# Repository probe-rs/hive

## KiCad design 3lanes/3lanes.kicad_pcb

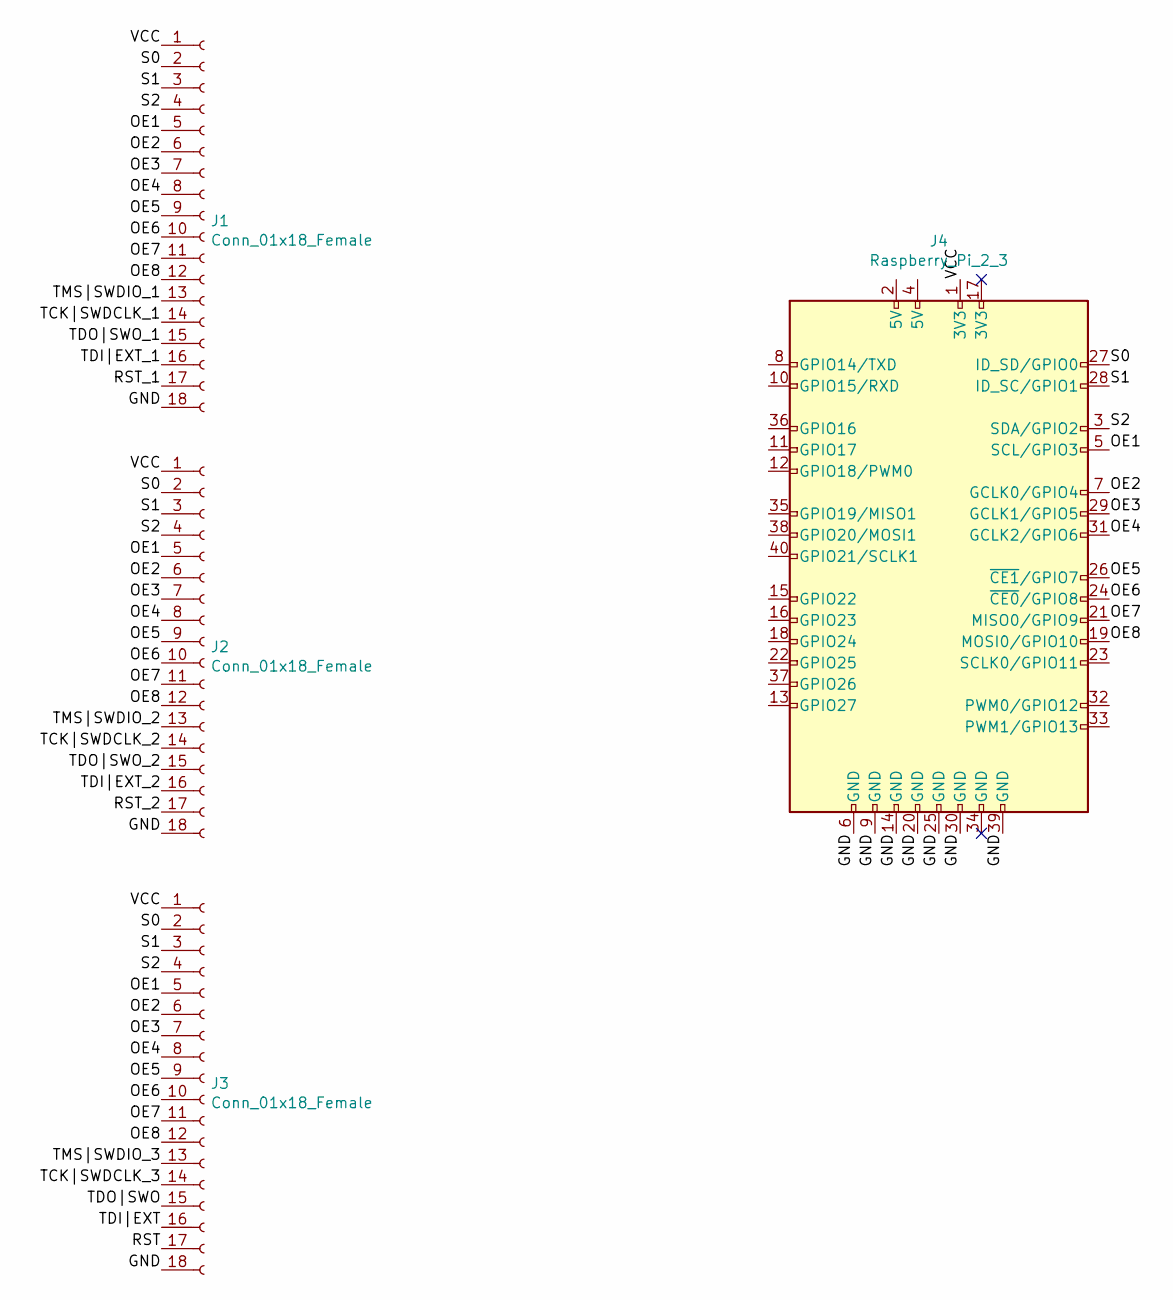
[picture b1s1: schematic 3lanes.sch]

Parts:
J1, J2, J3: Conn_01x18_Female
J4: Raspberry_Pi_2_3

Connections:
/GND: J1.18, J2.18, J3.18, J4.6 (GND), J4.9 (GND), J4.14 (GND), J4.20 (GND), J4.25 (GND), J4.30 (GND), J4.39 (GND)
/OE1: J1.5, J2.5, J3.5, J4.5 (SCL/GPIO3)
/OE2: J1.6, J2.6, J3.6, J4.7 (GCLK0/GPIO4)
/OE3: J1.7, J2.7, J3.7, J4.29 (GCLK1/GPIO5)
/OE4: J1.8, J2.8, J3.8, J4.31 (GCLK2/GPIO6)
/OE5: J1.9, J2.9, J3.9, J4.26 (~CE1~/GPIO7)
/OE6: J1.10, J2.10, J3.10, J4.24 (~CE0~/GPIO8)
/OE7: J1.11, J2.11, J3.11, J4.21 (MISO0/GPIO9)
/OE8: J1.12, J2.12, J3.12, J4.19 (MOSI0/GPIO10)
/RST: J3.17
/RST_1: J1.17
/RST_2: J2.17
/S0: J1.2, J2.2, J3.2, J4.27 (ID_SD/GPIO0)
/S1: J1.3, J2.3, J3.3, J4.28 (ID_SC/GPIO1)
/S2: J1.4, J2.4, J3.4, J4.3 (SDA/GPIO2)
/TCK|SWDCLK_1: J1.14
/TCK|SWDCLK_2: J2.14
/TCK|SWDCLK_3: J3.14
/TDI|EXT: J3.16
/TDI|EXT_1: J1.16
/TDI|EXT_2: J2.16
/TDO|SWO: J3.15
/TDO|SWO_1: J1.15
/TDO|SWO_2: J2.15
/TMS|SWDIO_1: J1.13
/TMS|SWDIO_2: J2.13
/TMS|SWDIO_3: J3.13
/VCC: J1.1, J2.1, J3.1, J4.1 (3V3)

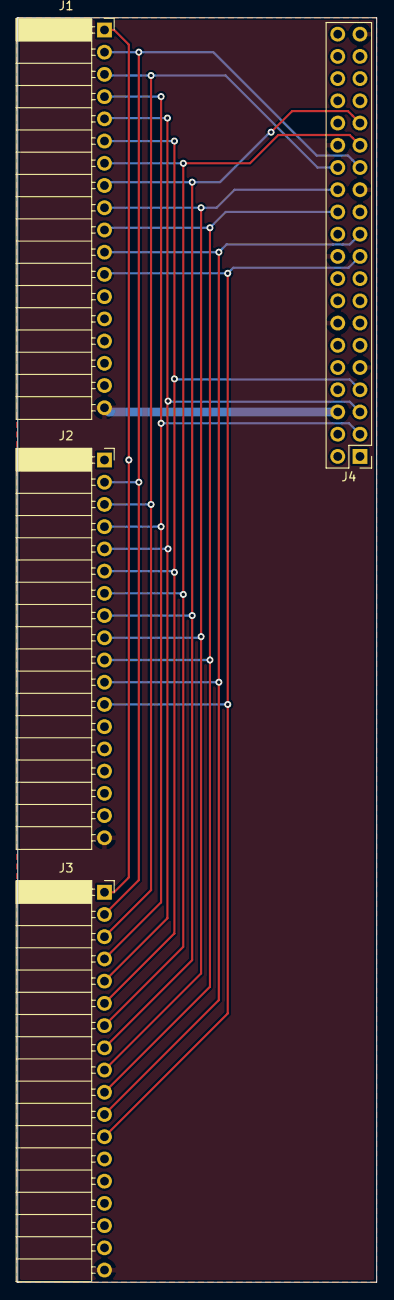
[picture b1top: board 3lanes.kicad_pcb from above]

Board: 2 copper layers, 41.0 x 144.5 mm, 4 parts (0 on the bottom side), 13 nets.

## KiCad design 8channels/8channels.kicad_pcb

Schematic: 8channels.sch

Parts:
C1, C2, C3, C4, C5: 0.1u; C_0402_1005Metric
C101, C102: 1u; C_0402_1005Metric
J1: Conn_01x18_Female; PinSocket_2x10_P2.54mm_Horizontal
J2: Conn_01x18_Male; PinHeader_2x10_P2.54mm_Horizontal
P1, P2: PCIEX1_02X18; 10018784-10200TLF
R101: 10k; R_0402_1005Metric
U1, U2, U3, U4, U5: SN74CB3Q3251PWR; R-PVQFN-N16
U101: MIC5353-3.3YMT; MLF-6-1EP_1.6x1.6mm_P0.5mm_EP0.5x1.26mm

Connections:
+5V: C101.1, J1.1, J2.1, U101.3
/OE: J2.5, R101.2, U1.7 (~OE), U2.7 (~OE), U3.7 (~OE), U4.7 (~OE), U5.7 (~OE), U101.1
/OE2: J1.5, J2.6
/OE3: J1.6, J2.7
/OE4: J1.7, J2.8
/OE5: J1.8, J2.9
/OE6: J1.9, J2.10
/OE7: J1.10, J2.11
/OE8: J1.11, J2.12
/RST: J1.19, J2.19, U5.5 (A)
/RST_1: P2.B15 (P30), U5.4 (B1)
/RST_2: P2.B11 (P22), U5.3 (B2)
/RST_3: P2.B7 (P14), U5.2 (B3)
/RST_4: P2.B3 (P6), U5.1 (B4)
/RST_5: P1.B15 (P30), U5.15 (B5)
/RST_6: P1.B11 (P22), U5.14 (B6)
/RST_7: P1.B7 (P14), U5.13 (B7)
/RST_8: P1.B3 (P6), U5.12 (B8)
/S0: J1.2, J2.2, U1.11 (S0), U2.11 (S0), U3.11 (S0), U4.11 (S0), U5.11 (S0)
/S1: J1.3, J2.3, U1.10 (S1), U2.10 (S1), U3.10 (S1), U4.10 (S1), U5.10 (S1)
/S2: J1.4, J2.4, U1.9 (S2), U2.9 (S2), U3.9 (S2), U4.9 (S2), U5.9 (S2)
/TCK|SWDCLK: J1.16, J2.16, U2.5 (A)
/TCK|SWDCLK_1: P2.A14 (P27), U2.4 (B1)
/TCK|SWDCLK_2: P2.A10 (P19), U2.3 (B2)
/TCK|SWDCLK_3: P2.A6 (P11), U2.2 (B3)
/TCK|SWDCLK_4: P2.A2 (P3), U2.1 (B4)
/TCK|SWDCLK_5: P1.A14 (P27), U2.15 (B5)
/TCK|SWDCLK_6: P1.A10 (P19), U2.14 (B6)
/TCK|SWDCLK_7: P1.A6 (P11), U2.13 (B7)
/TCK|SWDCLK_8: P1.A2 (P3), U2.12 (B8)
/TDI|EXT: J1.18, J2.18, U4.5 (A)
/TDI|EXT_1: P2.B14 (P28), U4.4 (B1)
/TDI|EXT_2: P2.B10 (P20), U4.3 (B2)
/TDI|EXT_3: P2.B6 (P12), U4.2 (B3)
/TDI|EXT_4: P2.B2 (P4), U4.1 (B4)
/TDI|EXT_5: P1.B14 (P28), U4.15 (B5)
/TDI|EXT_6: P1.B10 (P20), U4.14 (B6)
/TDI|EXT_7: P1.B6 (P12), U4.13 (B7)
/TDI|EXT_8: P1.B2 (P4), U4.12 (B8)
/TDO|SWO: J1.17, J2.17, U3.5 (A)
/TDO|SWO_1: P2.B13 (P26), U3.4 (B1)
/TDO|SWO_2: P2.B9 (P18), U3.3 (B2)
/TDO|SWO_3: P2.B5 (P10), U3.2 (B3)
/TDO|SWO_4: P2.B1 (P2), U3.1 (B4)
/TDO|SWO_5: P1.B13 (P26), U3.15 (B5)
/TDO|SWO_6: P1.B9 (P18), U3.14 (B6)
/TDO|SWO_7: P1.B5 (P10), U3.13 (B7)
/TDO|SWO_8: P1.B1 (P2), U3.12 (B8)
/TMS|SWDIO: J1.15, J2.15, U1.5 (A)
/TMS|SWDIO_1: P2.A13 (P25), U1.4 (B1)
/TMS|SWDIO_2: P2.A9 (P17), U1.3 (B2)
/TMS|SWDIO_3: P2.A5 (P9), U1.2 (B3)
/TMS|SWDIO_4: P2.A1 (P1), U1.1 (B4)
/TMS|SWDIO_5: P1.A13 (P25), U1.15 (B5)
/TMS|SWDIO_6: P1.A9 (P17), U1.14 (B6)
/TMS|SWDIO_7: P1.A5 (P9), U1.13 (B7)
/TMS|SWDIO_8: P1.A1 (P1), U1.12 (B8)

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
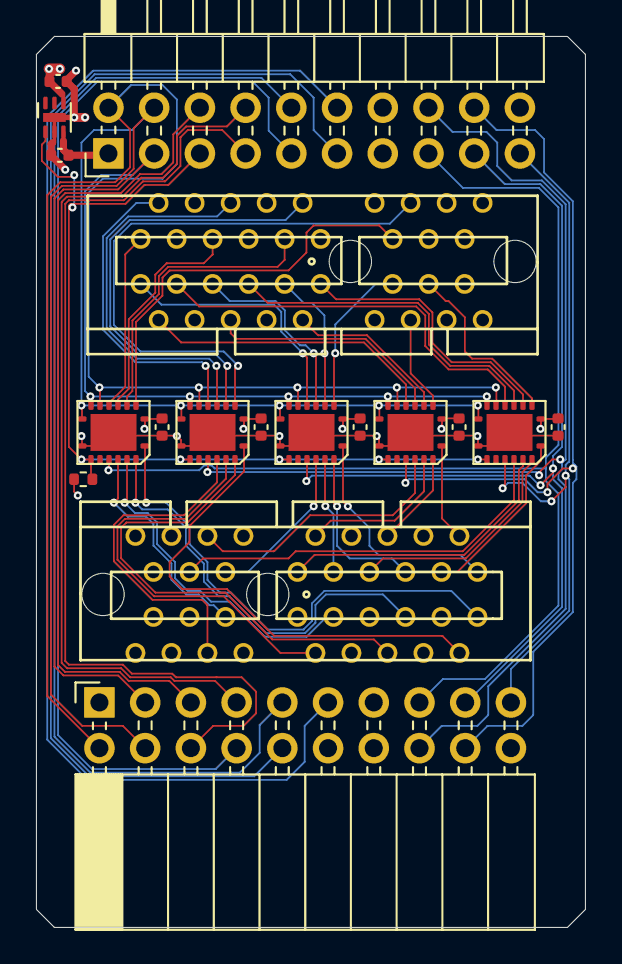
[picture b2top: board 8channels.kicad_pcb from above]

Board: 4 copper layers, 30.5 x 49.5 mm, 18 parts (0 on the bottom side), 59 nets.

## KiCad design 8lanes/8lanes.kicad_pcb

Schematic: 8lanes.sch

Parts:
C101, C102: 47u; C_1206_3216Metric
C103, C104, C105, C106, C107, C108, C109, C110, C111, C112, C113, C114, C115, C116: 0.1u; C_0402_1005Metric
J101, J102, J105, J106, J109, J110, J113, J114: Conn_01x20_Female; PinSocket_2x10_P2.54mm_Horizontal
J103, J104, J107, J108, J111, J112, J115, J116: Conn_ARM_JTAG_SWD_20; PinSocket_2x10_P2.54mm_Vertical
J117: Raspberry_Pi_2_3; PinHeader_2x20_P2.54mm_Vertical
J118, J119, J120, J121, J122, J123, J124, J125: Conn_ST_STDC14; PinHeader_2x07_P1.27mm_Vertical_SMD
R101: 100; R_0402_1005Metric
U101, U102, U103, U104, U105, U106, U107, U108, U109, U110, U111, U112, U113, U114: SN74CB3Q3251PWR; R-PVQFN-N16

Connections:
+3V3: C103.1, C104.1, C105.1, C106.1, C107.1, C108.1, C109.1, C110.1, C111.1, C112.1, C113.1, C114.1, C115.1, C116.1, J103.1, J104.1, J107.1, J108.1, J111.1, J112.1, J115.1, J116.1, J117.1 (3V3), J117.17 (3V3), J118.3, J119.3, J120.3, J121.3, J122.3, J123.3, J124.3, J125.3, R101.1, U101.16 (VCC), U102.16 (VCC), U103.16 (VCC), U104.16 (VCC), U105.16 (VCC), U106.16 (VCC), U107.16 (VCC), U108.16 (VCC), U109.16 (VCC), U110.16 (VCC), U111.16 (VCC), U112.16 (VCC), U113.16 (VCC), U114.16 (VCC)
+5V: C101.1, C102.1, J101.1, J102.1, J105.1, J106.1, J109.1, J110.1, J113.1, J114.1, J117.2 (5V), J117.4 (5V)
/LANE_S0: J117.33 (PWM1/GPIO13), U109.11 (S0)
/LANE_S1: J117.35 (GPIO19/MISO1), U109.10 (S1)
/LANE_S2: J117.36 (GPIO16), U109.9 (S2)
/MCU_S0: J101.10, J102.10, J105.10, J106.10, J109.10, J110.10, J113.10, J114.10, J117.37 (GPIO26)
/MCU_S1: J101.11, J102.11, J105.11, J106.11, J109.11, J110.11, J113.11, J114.11, J117.38 (GPIO20/MOSI1)
/MCU_S2: J101.12, J102.12, J105.12, J106.12, J109.12, J110.12, J113.12, J114.12, J117.40 (GPIO21/SCLK1)
/OE_LANE1: U101.5 (A), U109.4 (B1)
/OE_LANE2: U103.5 (A), U109.3 (B2)
/OE_LANE3: U105.5 (A), U109.2 (B3)
/OE_LANE4: U107.5 (A), U109.1 (B4)
/OE_LANE5: U102.5 (A), U109.15 (B5)
/OE_LANE6: U104.5 (A), U109.14 (B6)
/OE_LANE7: U106.5 (A), U109.13 (B7)
/OE_LANE8: U108.5 (A), U109.12 (B8)
/PROBE_S0: J117.11 (GPIO17), U110.11 (S0), U111.11 (S0), U112.11 (S0), U113.11 (S0), U114.11 (S0)
/PROBE_S1: J117.12 (GPIO18/PWM0), U110.10 (S1), U111.10 (S1), U112.10 (S1), U113.10 (S1), U114.10 (S1)
/PROBE_S2: J117.13 (GPIO27), U110.9 (S2), U111.9 (S2), U112.9 (S2), U113.9 (S2), U114.9 (S2)
/ROW_S0: J117.31 (GCLK2/GPIO6), U101.11 (S0), U102.11 (S0), U103.11 (S0), U104.11 (S0), U105.11 (S0), U106.11 (S0), U107.11 (S0), U108.11 (S0)
/ROW_S1: J117.29 (GCLK1/GPIO5), U101.10 (S1), U102.10 (S1), U103.10 (S1), U104.10 (S1), U105.10 (S1), U106.10 (S1), U107.10 (S1), U108.10 (S1)
/ROW_S2: J117.28 (ID_SC/GPIO1), U101.9 (S2), U102.9 (S2), U103.9 (S2), U104.9 (S2), U105.9 (S2), U106.9 (S2), U107.9 (S2), U108.9 (S2)
/RST: J101.19, J102.19, J105.19, J106.19, J109.19, J110.19, J113.19, J114.19, U114.5 (A)
/RST_P_1: J103.15, J118.12, U114.12 (B8)
/RST_P_2: J107.15, J119.12, U114.13 (B7)
/RST_P_3: J111.15, J120.12, U114.14 (B6)
/RST_P_4: J115.15, J121.12, U114.15 (B5)
/RST_P_5: J104.15, J122.12, U114.1 (B4)
/RST_P_6: J108.15, J123.12, U114.2 (B3)
/RST_P_7: J112.15, J124.12, U114.3 (B2)
/RST_P_8: J116.15, J125.12, U114.4 (B1)
/TCK|SWDCLK: J101.16, J102.16, J105.16, J106.16, J109.16, J110.16, J113.16, J114.16, U111.5 (A)
/TCK|SWDCLK_P_1: J103.9, J118.6, U111.12 (B8)
/TCK|SWDCLK_P_2: J107.9, J119.6, U111.13 (B7)
/TCK|SWDCLK_P_3: J111.9, J120.6, U111.14 (B6)
/TCK|SWDCLK_P_4: J115.9, J121.6, U111.15 (B5)
/TCK|SWDCLK_P_5: J104.9, J122.6, U111.1 (B4)
/TCK|SWDCLK_P_6: J108.9, J123.6, U111.2 (B3)
/TCK|SWDCLK_P_7: J112.9, J124.6, U111.3 (B2)
/TCK|SWDCLK_P_8: J116.9, J125.6, U111.4 (B1)
/TDI|EXT: J101.18, J102.18, J105.18, J106.18, J109.18, J110.18, J113.18, J114.18, U113.5 (A)
/TDI|EXT_P_1: J103.5, J118.10, U113.12 (B8)
/TDI|EXT_P_2: J107.5, J119.10, U113.13 (B7)
/TDI|EXT_P_3: J111.5, J120.10, U113.14 (B6)
/TDI|EXT_P_4: J115.5, J121.10, U113.15 (B5)
/TDI|EXT_P_5: J104.5, J122.10, U113.1 (B4)
/TDI|EXT_P_6: J108.5, J123.10, U113.2 (B3)
/TDI|EXT_P_7: J112.5, J124.10, U113.3 (B2)
/TDI|EXT_P_8: J116.5, J125.10, U113.4 (B1)
/TDO|SWO: J101.17, J102.17, J105.17, J106.17, J109.17, J110.17, J113.17, J114.17, U112.5 (A)
/TDO|SWO_P_1: J103.13, J118.8, U112.12 (B8)
/TDO|SWO_P_2: J107.13, J119.8, U112.13 (B7)
/TDO|SWO_P_3: J111.13, J120.8, U112.14 (B6)
/TDO|SWO_P_4: J115.13, J121.8, U112.15 (B5)
/TDO|SWO_P_5: J104.13, J122.8, U112.1 (B4)
/TDO|SWO_P_6: J108.13, J123.8, U112.2 (B3)
/TDO|SWO_P_7: J112.13, J124.8, U112.3 (B2)
/TDO|SWO_P_8: J116.13, J125.8, U112.4 (B1)
/TMS|SWDIO: J101.15, J102.15, J105.15, J106.15, J109.15, J110.15, J113.15, J114.15, U110.5 (A)
/TMS|SWDIO_P_1: J103.7, J118.4, U110.12 (B8)
/TMS|SWDIO_P_2: J107.7, J119.4, U110.13 (B7)
/TMS|SWDIO_P_3: J111.7, J120.4, U110.14 (B6)
/TMS|SWDIO_P_4: J115.7, J121.4, U110.15 (B5)
/TMS|SWDIO_P_5: J104.7, J122.4, U110.1 (B4)
/TMS|SWDIO_P_6: J108.7, J123.4, U110.2 (B3)
/TMS|SWDIO_P_7: J112.7, J124.4, U110.3 (B2)
/TMS|SWDIO_P_8: J116.7, J125.4, U110.4 (B1)
GND: C101.2, C102.2, C103.2, C104.2, C105.2, C106.2, C107.2, C108.2, C109.2, C110.2, C111.2, C112.2, C113.2, C114.2, C115.2, C116.2, J101.13, J101.14, J101.20, J102.13, J102.14, J102.20, J103.4, J103.6, J103.8, J103.10, J103.12, J103.14, J103.16, J103.18, J103.20, J104.4, J104.6, J104.8, J104.10, J104.12, J104.14, J104.16, J104.18, J104.20, J105.13, J105.14, J105.20, J106.13, J106.14, J106.20, J107.4, J107.6, J107.8, J107.10, J107.12, J107.14, J107.16, J107.18, J107.20, J108.4, J108.6, J108.8, J108.10, J108.12, J108.14, J108.16, J108.18, J108.20, J109.13, J109.14, J109.20, J110.13, J110.14, J110.20, J111.4, J111.6, J111.8, J111.10, J111.12, J111.14, J111.16, J111.18, J111.20, J112.4, J112.6, J112.8, J112.10, J112.12, J112.14, J112.16, J112.18, J112.20, J113.13, J113.14, J113.20, J114.13, J114.14, J114.20, J115.4, J115.6, J115.8, J115.10, J115.12, J115.14, J115.16, J115.18, J115.20, J116.4, J116.6, J116.8, J116.10, J116.12, J116.14, J116.16, J116.18, J116.20, J117.6 (GND), J117.9 (GND), J117.14 (GND), J117.20 (GND), J117.25 (GND), J117.30 (GND), J117.34 (GND), J117.39 (GND), J118.5, J118.7, J118.11, J119.5, J119.7, J119.11, J120.5, J120.7, J120.11, J121.5, J121.7, J121.11, J122.5, J122.7, J122.11, J123.5, J123.7, J123.11, J124.5, J124.7, J124.11, J125.5, J125.7, J125.11, U101.0, U101.7 (~OE), U101.8 (GND), U102.0, U102.7 (~OE), U102.8 (GND), U103.0, U103.7 (~OE), U103.8 (GND), U104.0, U104.7 (~OE), U104.8 (GND), U105.0, U105.7 (~OE), U105.8 (GND), U106.0, U106.7 (~OE), U106.8 (GND), U107.0, U107.7 (~OE), U107.8 (GND), U108.0, U108.7 (~OE), U108.8 (GND), U109.0, U109.7 (~OE), U109.8 (GND), U110.0, U110.7 (~OE), U110.8 (GND), U111.0, U111.7 (~OE), U111.8 (GND), U112.0, U112.7 (~OE), U112.8 (GND), U113.0, U113.7 (~OE), U113.8 (GND), U114.0, U114.7 (~OE), U114.8 (GND)
unnamed: J101.2, U101.12 (B8)
unnamed: J101.3, U101.13 (B7)
unnamed: J101.4, U101.14 (B6)
unnamed: J101.5, U101.15 (B5)
unnamed: J101.6, U101.1 (B4)
unnamed: J101.7, U101.2 (B3)
unnamed: J101.8, U101.3 (B2)
unnamed: J101.9, U101.4 (B1)
unnamed: J102.2, U102.12 (B8)
unnamed: J102.3, U102.13 (B7)
unnamed: J102.4, U102.14 (B6)
unnamed: J102.5, U102.15 (B5)
unnamed: J102.6, U102.1 (B4)
unnamed: J102.7, U102.2 (B3)
unnamed: J102.8, U102.3 (B2)
unnamed: J102.9, U102.4 (B1)
unnamed: J105.2, U103.12 (B8)
unnamed: J105.3, U103.13 (B7)
unnamed: J105.4, U103.14 (B6)
unnamed: J105.5, U103.15 (B5)
unnamed: J105.6, U103.1 (B4)
unnamed: J105.7, U103.2 (B3)
unnamed: J105.8, U103.3 (B2)
unnamed: J105.9, U103.4 (B1)
unnamed: J106.2, U104.12 (B8)
unnamed: J106.3, U104.13 (B7)
unnamed: J106.4, U104.14 (B6)
unnamed: J106.5, U104.15 (B5)
unnamed: J106.6, U104.1 (B4)
unnamed: J106.7, U104.2 (B3)
unnamed: J106.8, U104.3 (B2)
unnamed: J106.9, U104.4 (B1)
unnamed: J109.2, U105.12 (B8)
unnamed: J109.3, U105.13 (B7)
unnamed: J109.4, U105.14 (B6)
unnamed: J109.5, U105.15 (B5)
unnamed: J109.6, U105.1 (B4)
unnamed: J109.7, U105.2 (B3)
unnamed: J109.8, U105.3 (B2)
unnamed: J109.9, U105.4 (B1)
unnamed: J110.2, U106.12 (B8)
unnamed: J110.3, U106.13 (B7)
unnamed: J110.4, U106.14 (B6)
unnamed: J110.5, U106.15 (B5)
unnamed: J110.6, U106.1 (B4)
unnamed: J110.7, U106.2 (B3)
unnamed: J110.8, U106.3 (B2)
unnamed: J110.9, U106.4 (B1)
unnamed: J113.2, U107.12 (B8)
unnamed: J113.3, U107.13 (B7)
unnamed: J113.4, U107.14 (B6)
unnamed: J113.5, U107.15 (B5)
unnamed: J113.6, U107.1 (B4)
unnamed: J113.7, U107.2 (B3)
unnamed: J113.8, U107.3 (B2)
unnamed: J113.9, U107.4 (B1)
unnamed: J114.2, U108.12 (B8)
unnamed: J114.3, U108.13 (B7)
unnamed: J114.4, U108.14 (B6)
unnamed: J114.5, U108.15 (B5)
unnamed: J114.6, U108.1 (B4)
unnamed: J114.7, U108.2 (B3)
unnamed: J114.8, U108.3 (B2)
unnamed: J114.9, U108.4 (B1)
unnamed: R101.2, U109.5 (A)

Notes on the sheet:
OE Lane Driver
Probe Bus Multiplexer
OE Row Driver
OE Drivers
8 Probe -> 512 Slave MCUs
Probe Connections

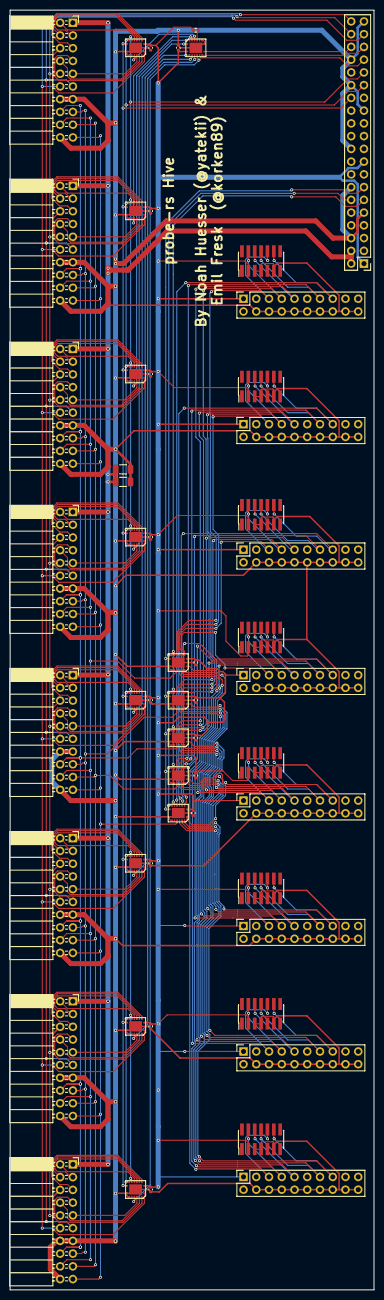
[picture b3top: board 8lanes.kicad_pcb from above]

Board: 4 copper layers, 72.5 x 255.0 mm, 56 parts (0 on the bottom side), 133 nets.

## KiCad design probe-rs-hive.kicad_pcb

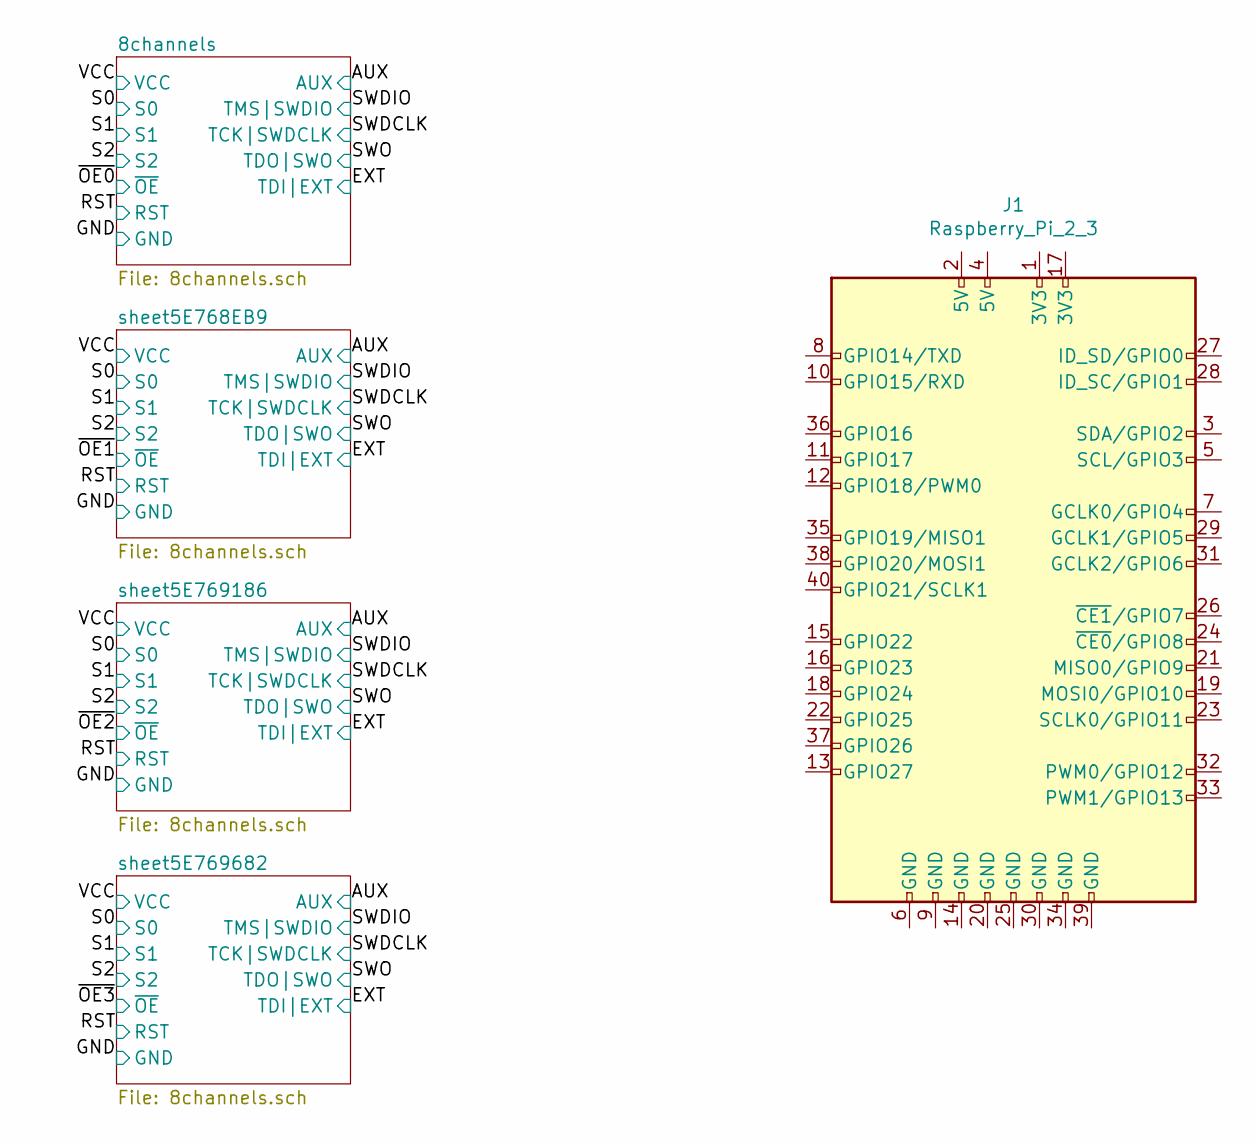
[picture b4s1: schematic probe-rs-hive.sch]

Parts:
J1: Raspberry_Pi_2_3; PinSocket_2x20_P2.54mm_Vertical

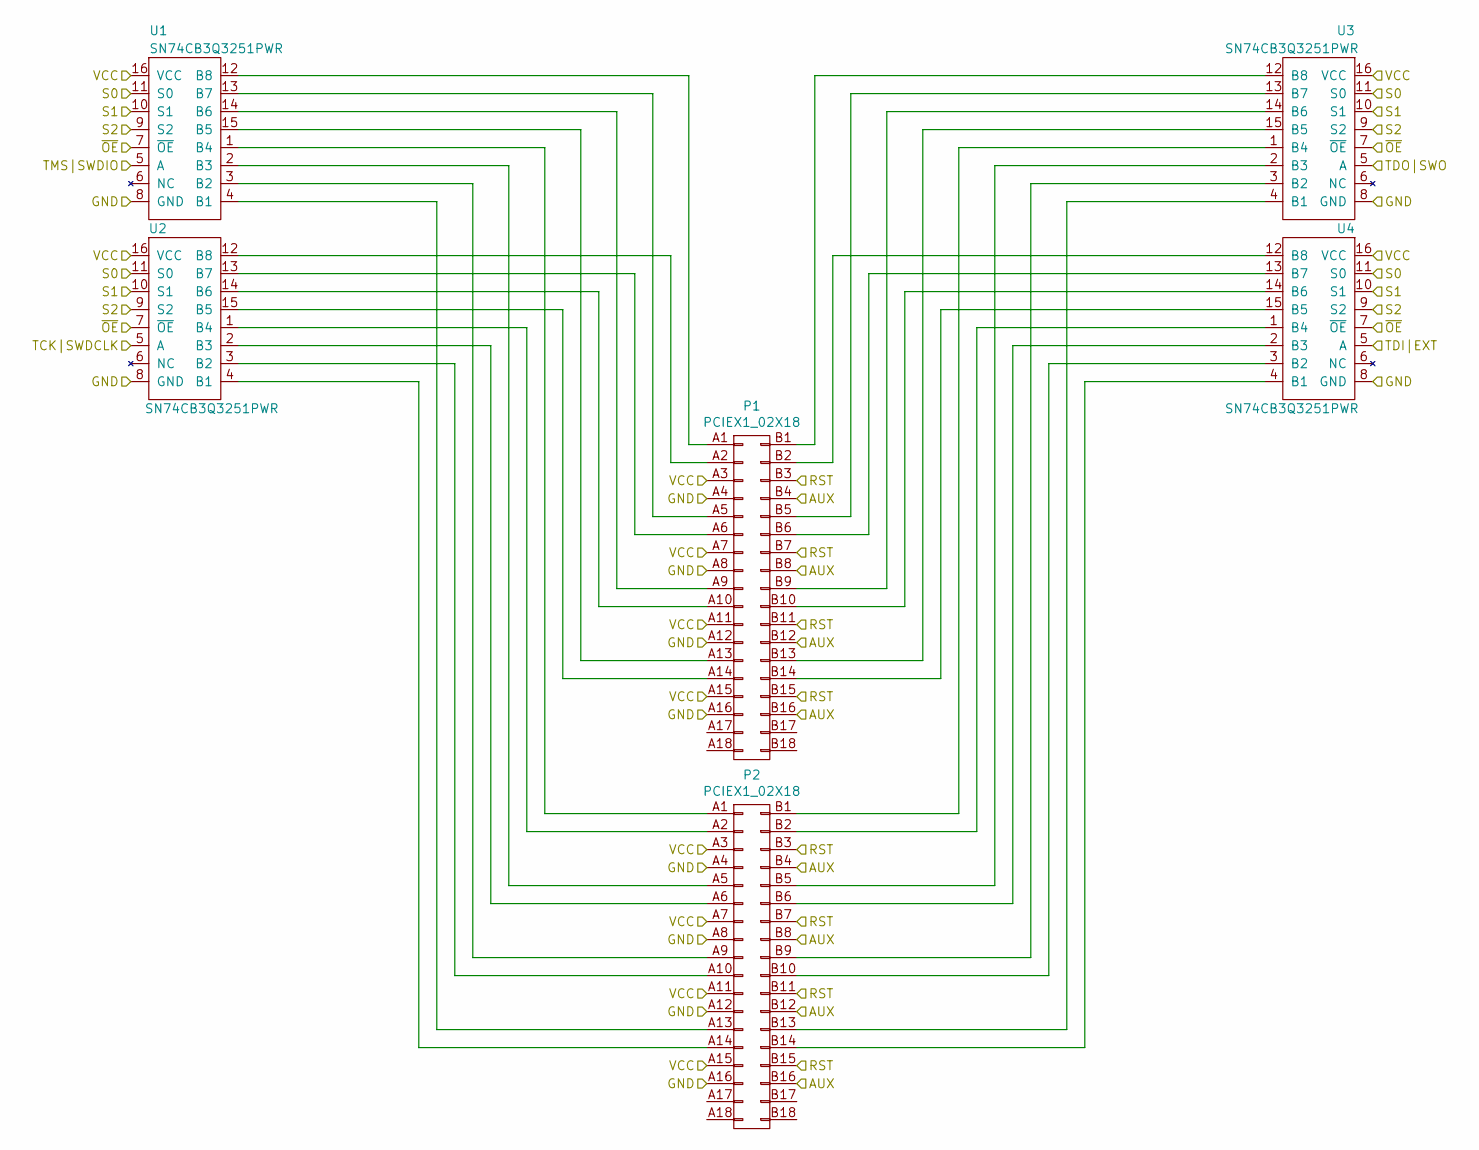
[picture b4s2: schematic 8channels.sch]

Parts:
P1, P2: PCIEX1_02X18; 10018784-10200TLF
U1, U2, U3, U4: SN74CB3Q3251PWR; R-PVQFN-N16

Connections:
/AUX: P1.B4 (P8), P1.B8 (P16), P1.B12 (P24), P1.B16 (P32), P2.B4 (P8), P2.B8 (P16), P2.B12 (P24), P2.B16 (P32); also elsewhere on the board
/EXT: U4.5 (A); also elsewhere on the board
/GND: P1.A4 (P7), P1.A8 (P15), P1.A12 (P23), P1.A16 (P31), P2.A4 (P7), P2.A8 (P15), P2.A12 (P23), P2.A16 (P31), U1.8 (GND), U2.8 (GND), U3.8 (GND), U4.8 (GND); also elsewhere on the board
/RST: P1.B3 (P6), P1.B7 (P14), P1.B11 (P22), P1.B15 (P30), P2.B3 (P6), P2.B7 (P14), P2.B11 (P22), P2.B15 (P30); also elsewhere on the board
/S0: U1.11 (S0), U2.11 (S0), U3.11 (S0), U4.11 (S0); also elsewhere on the board
/S1: U1.10 (S1), U2.10 (S1), U3.10 (S1), U4.10 (S1); also elsewhere on the board
/S2: U1.9 (S2), U2.9 (S2), U3.9 (S2), U4.9 (S2); also elsewhere on the board
/SWDCLK: U2.5 (A); also elsewhere on the board
/SWDIO: U1.5 (A); also elsewhere on the board
/SWO: U3.5 (A); also elsewhere on the board
/VCC: P1.A3 (P5), P1.A7 (P13), P1.A11 (P21), P1.A15 (P29), P2.A3 (P5), P2.A7 (P13), P2.A11 (P21), P2.A15 (P29), U1.16 (VCC), U2.16 (VCC), U3.16 (VCC), U4.16 (VCC); also elsewhere on the board
/~OE0: U1.7 (~OE), U2.7 (~OE), U3.7 (~OE), U4.7 (~OE)
unnamed: P1.A1 (P1), U1.12 (B8)
unnamed: P1.A2 (P3), U2.12 (B8)
unnamed: P1.A5 (P9), U1.13 (B7)
unnamed: P1.A6 (P11), U2.13 (B7)
unnamed: P1.A9 (P17), U1.14 (B6)
unnamed: P1.A10 (P19), U2.14 (B6)
unnamed: P1.A13 (P25), U1.15 (B5)
unnamed: P1.A14 (P27), U2.15 (B5)
unnamed: P1.B1 (P2), U3.12 (B8)
unnamed: P1.B2 (P4), U4.12 (B8)
unnamed: P1.B5 (P10), U3.13 (B7)
unnamed: P1.B6 (P12), U4.13 (B7)
unnamed: P1.B9 (P18), U3.14 (B6)
unnamed: P1.B10 (P20), U4.14 (B6)
unnamed: P1.B13 (P26), U3.15 (B5)
unnamed: P1.B14 (P28), U4.15 (B5)
unnamed: P2.A1 (P1), U1.1 (B4)
unnamed: P2.A2 (P3), U2.1 (B4)
unnamed: P2.A5 (P9), U1.2 (B3)
unnamed: P2.A6 (P11), U2.2 (B3)
unnamed: P2.A9 (P17), U1.3 (B2)
unnamed: P2.A10 (P19), U2.3 (B2)
unnamed: P2.A13 (P25), U1.4 (B1)
unnamed: P2.A14 (P27), U2.4 (B1)
unnamed: P2.B1 (P2), U3.1 (B4)
unnamed: P2.B2 (P4), U4.1 (B4)
unnamed: P2.B5 (P10), U3.2 (B3)
unnamed: P2.B6 (P12), U4.2 (B3)
unnamed: P2.B9 (P18), U3.3 (B2)
unnamed: P2.B10 (P20), U4.3 (B2)
unnamed: P2.B13 (P26), U3.4 (B1)
unnamed: P2.B14 (P28), U4.4 (B1)

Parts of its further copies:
P3, P4, P5, P6, P7, P8: PCIEX1_02X18; 10018784-10200TLF
U5, U6, U7, U8, U9, U10, U11, U12, U13, U14, U15, U16: SN74CB3Q3251PWR; R-PVQFN-N16

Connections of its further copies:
/AUX: P3.B4 (P8), P3.B8 (P16), P3.B12 (P24), P3.B16 (P32), P4.B4 (P8), P4.B8 (P16), P4.B12 (P24), P4.B16 (P32), P5.B4 (P8), P5.B8 (P16), P5.B12 (P24), P5.B16 (P32), P6.B4 (P8), P6.B8 (P16), P6.B12 (P24), P6.B16 (P32), P7.B4 (P8), P7.B8 (P16), P7.B12 (P24), P7.B16 (P32), P8.B4 (P8), P8.B8 (P16), P8.B12 (P24), P8.B16 (P32); also elsewhere on the board
/EXT: U8.5 (A), U12.5 (A), U16.5 (A); also elsewhere on the board
/GND: P3.A4 (P7), P3.A8 (P15), P3.A12 (P23), P3.A16 (P31), P4.A4 (P7), P4.A8 (P15), P4.A12 (P23), P4.A16 (P31), P5.A4 (P7), P5.A8 (P15), P5.A12 (P23), P5.A16 (P31), P6.A4 (P7), P6.A8 (P15), P6.A12 (P23), P6.A16 (P31), P7.A4 (P7), P7.A8 (P15), P7.A12 (P23), P7.A16 (P31), P8.A4 (P7), P8.A8 (P15), P8.A12 (P23), P8.A16 (P31), U5.8 (GND), U6.8 (GND), U7.8 (GND), U8.8 (GND), U9.8 (GND), U10.8 (GND), U11.8 (GND), U12.8 (GND), U13.8 (GND), U14.8 (GND), U15.8 (GND), U16.8 (GND); also elsewhere on the board
/RST: P3.B3 (P6), P3.B7 (P14), P3.B11 (P22), P3.B15 (P30), P4.B3 (P6), P4.B7 (P14), P4.B11 (P22), P4.B15 (P30), P5.B3 (P6), P5.B7 (P14), P5.B11 (P22), P5.B15 (P30), P6.B3 (P6), P6.B7 (P14), P6.B11 (P22), P6.B15 (P30), P7.B3 (P6), P7.B7 (P14), P7.B11 (P22), P7.B15 (P30), P8.B3 (P6), P8.B7 (P14), P8.B11 (P22), P8.B15 (P30); also elsewhere on the board
/S0: U5.11 (S0), U6.11 (S0), U7.11 (S0), U8.11 (S0), U9.11 (S0), U10.11 (S0), U11.11 (S0), U12.11 (S0), U13.11 (S0), U14.11 (S0), U15.11 (S0), U16.11 (S0); also elsewhere on the board
/S1: U5.10 (S1), U6.10 (S1), U7.10 (S1), U8.10 (S1), U9.10 (S1), U10.10 (S1), U11.10 (S1), U12.10 (S1), U13.10 (S1), U14.10 (S1), U15.10 (S1), U16.10 (S1); also elsewhere on the board
/S2: U5.9 (S2), U6.9 (S2), U7.9 (S2), U8.9 (S2), U9.9 (S2), U10.9 (S2), U11.9 (S2), U12.9 (S2), U13.9 (S2), U14.9 (S2), U15.9 (S2), U16.9 (S2); also elsewhere on the board
/SWDCLK: U6.5 (A), U10.5 (A), U14.5 (A); also elsewhere on the board
/SWDIO: U5.5 (A), U9.5 (A), U13.5 (A); also elsewhere on the board
/SWO: U7.5 (A), U11.5 (A), U15.5 (A); also elsewhere on the board
/VCC: P3.A3 (P5), P3.A7 (P13), P3.A11 (P21), P3.A15 (P29), P4.A3 (P5), P4.A7 (P13), P4.A11 (P21), P4.A15 (P29), P5.A3 (P5), P5.A7 (P13), P5.A11 (P21), P5.A15 (P29), P6.A3 (P5), P6.A7 (P13), P6.A11 (P21), P6.A15 (P29), P7.A3 (P5), P7.A7 (P13), P7.A11 (P21), P7.A15 (P29), P8.A3 (P5), P8.A7 (P13), P8.A11 (P21), P8.A15 (P29), U5.16 (VCC), U6.16 (VCC), U7.16 (VCC), U8.16 (VCC), U9.16 (VCC), U10.16 (VCC), U11.16 (VCC), U12.16 (VCC), U13.16 (VCC), U14.16 (VCC), U15.16 (VCC), U16.16 (VCC); also elsewhere on the board
/~OE1: U5.7 (~OE), U6.7 (~OE), U7.7 (~OE), U8.7 (~OE)
/~OE2: U9.7 (~OE), U10.7 (~OE), U11.7 (~OE), U12.7 (~OE)
/~OE3: U13.7 (~OE), U14.7 (~OE), U15.7 (~OE), U16.7 (~OE)
unnamed: P3.A1 (P1), U5.12 (B8)
unnamed: P3.A2 (P3), U6.12 (B8)
unnamed: P3.A5 (P9), U5.13 (B7)
unnamed: P3.A6 (P11), U6.13 (B7)
unnamed: P3.A9 (P17), U5.14 (B6)
unnamed: P3.A10 (P19), U6.14 (B6)
unnamed: P3.A13 (P25), U5.15 (B5)
unnamed: P3.A14 (P27), U6.15 (B5)
unnamed: P3.B1 (P2), U7.12 (B8)
unnamed: P3.B2 (P4), U8.12 (B8)
unnamed: P3.B5 (P10), U7.13 (B7)
unnamed: P3.B6 (P12), U8.13 (B7)
unnamed: P3.B9 (P18), U7.14 (B6)
unnamed: P3.B10 (P20), U8.14 (B6)
unnamed: P3.B13 (P26), U7.15 (B5)
unnamed: P3.B14 (P28), U8.15 (B5)
unnamed: P4.A1 (P1), U5.1 (B4)
unnamed: P4.A2 (P3), U6.1 (B4)
unnamed: P4.A5 (P9), U5.2 (B3)
unnamed: P4.A6 (P11), U6.2 (B3)
unnamed: P4.A9 (P17), U5.3 (B2)
unnamed: P4.A10 (P19), U6.3 (B2)
unnamed: P4.A13 (P25), U5.4 (B1)
unnamed: P4.A14 (P27), U6.4 (B1)
unnamed: P4.B1 (P2), U7.1 (B4)
unnamed: P4.B2 (P4), U8.1 (B4)
unnamed: P4.B5 (P10), U7.2 (B3)
unnamed: P4.B6 (P12), U8.2 (B3)
unnamed: P4.B9 (P18), U7.3 (B2)
unnamed: P4.B10 (P20), U8.3 (B2)
unnamed: P4.B13 (P26), U7.4 (B1)
unnamed: P4.B14 (P28), U8.4 (B1)
unnamed: P5.A1 (P1), U9.12 (B8)
unnamed: P5.A2 (P3), U10.12 (B8)
unnamed: P5.A5 (P9), U9.13 (B7)
unnamed: P5.A6 (P11), U10.13 (B7)
unnamed: P5.A9 (P17), U9.14 (B6)
unnamed: P5.A10 (P19), U10.14 (B6)
unnamed: P5.A13 (P25), U9.15 (B5)
unnamed: P5.A14 (P27), U10.15 (B5)
unnamed: P5.B1 (P2), U11.12 (B8)
unnamed: P5.B2 (P4), U12.12 (B8)
unnamed: P5.B5 (P10), U11.13 (B7)
unnamed: P5.B6 (P12), U12.13 (B7)
unnamed: P5.B9 (P18), U11.14 (B6)
unnamed: P5.B10 (P20), U12.14 (B6)
unnamed: P5.B13 (P26), U11.15 (B5)
unnamed: P5.B14 (P28), U12.15 (B5)
unnamed: P6.A1 (P1), U9.1 (B4)
unnamed: P6.A2 (P3), U10.1 (B4)
unnamed: P6.A5 (P9), U9.2 (B3)
unnamed: P6.A6 (P11), U10.2 (B3)
unnamed: P6.A9 (P17), U9.3 (B2)
unnamed: P6.A10 (P19), U10.3 (B2)
unnamed: P6.A13 (P25), U9.4 (B1)
unnamed: P6.A14 (P27), U10.4 (B1)
unnamed: P6.B1 (P2), U11.1 (B4)
unnamed: P6.B2 (P4), U12.1 (B4)
unnamed: P6.B5 (P10), U11.2 (B3)
unnamed: P6.B6 (P12), U12.2 (B3)
unnamed: P6.B9 (P18), U11.3 (B2)
unnamed: P6.B10 (P20), U12.3 (B2)
unnamed: P6.B13 (P26), U11.4 (B1)
unnamed: P6.B14 (P28), U12.4 (B1)
unnamed: P7.A1 (P1), U13.12 (B8)
unnamed: P7.A2 (P3), U14.12 (B8)
unnamed: P7.A5 (P9), U13.13 (B7)
unnamed: P7.A6 (P11), U14.13 (B7)
unnamed: P7.A9 (P17), U13.14 (B6)
unnamed: P7.A10 (P19), U14.14 (B6)
unnamed: P7.A13 (P25), U13.15 (B5)
unnamed: P7.A14 (P27), U14.15 (B5)
unnamed: P7.B1 (P2), U15.12 (B8)
unnamed: P7.B2 (P4), U16.12 (B8)
unnamed: P7.B5 (P10), U15.13 (B7)
unnamed: P7.B6 (P12), U16.13 (B7)
unnamed: P7.B9 (P18), U15.14 (B6)
unnamed: P7.B10 (P20), U16.14 (B6)
unnamed: P7.B13 (P26), U15.15 (B5)
unnamed: P7.B14 (P28), U16.15 (B5)
unnamed: P8.A1 (P1), U13.1 (B4)
unnamed: P8.A2 (P3), U14.1 (B4)
unnamed: P8.A5 (P9), U13.2 (B3)
unnamed: P8.A6 (P11), U14.2 (B3)
unnamed: P8.A9 (P17), U13.3 (B2)
unnamed: P8.A10 (P19), U14.3 (B2)
unnamed: P8.A13 (P25), U13.4 (B1)
unnamed: P8.A14 (P27), U14.4 (B1)
unnamed: P8.B1 (P2), U15.1 (B4)
unnamed: P8.B2 (P4), U16.1 (B4)
unnamed: P8.B5 (P10), U15.2 (B3)
unnamed: P8.B6 (P12), U16.2 (B3)
unnamed: P8.B9 (P18), U15.3 (B2)
unnamed: P8.B10 (P20), U16.3 (B2)
unnamed: P8.B13 (P26), U15.4 (B1)
unnamed: P8.B14 (P28), U16.4 (B1)

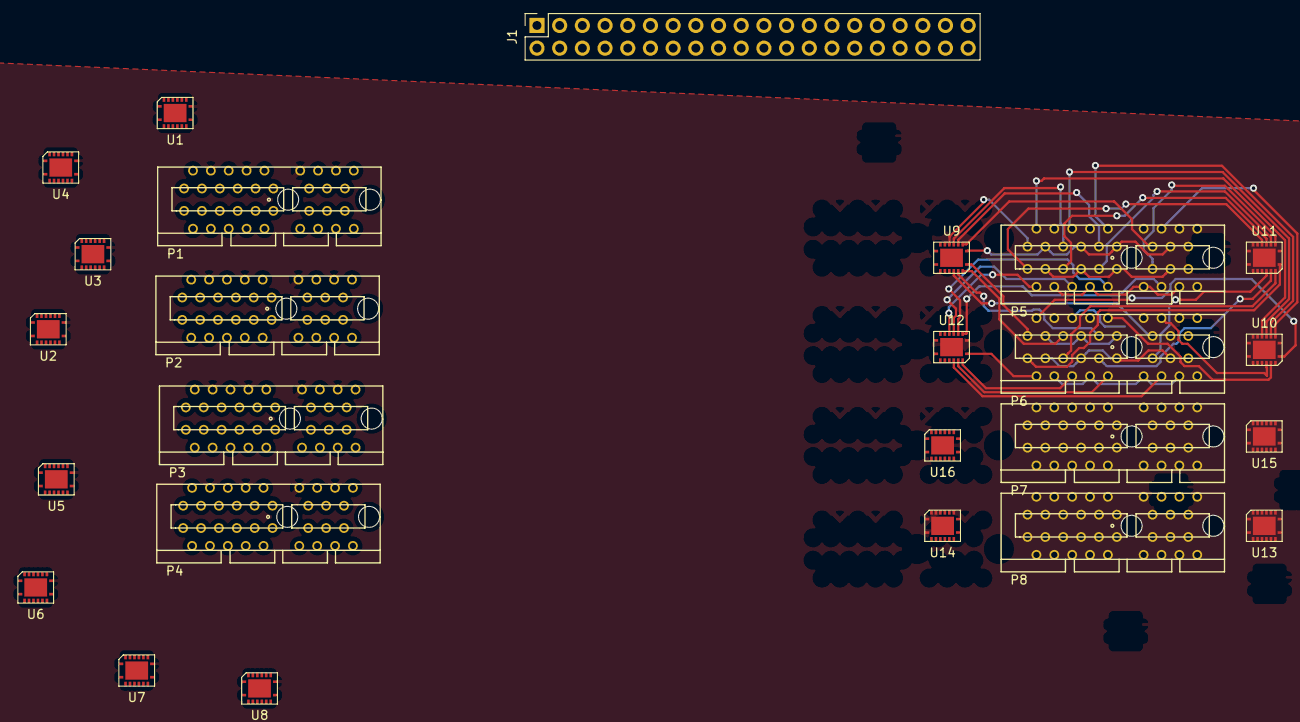
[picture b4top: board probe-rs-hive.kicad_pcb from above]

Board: 2 copper layers, 25 parts (0 on the bottom side), 143 nets.
